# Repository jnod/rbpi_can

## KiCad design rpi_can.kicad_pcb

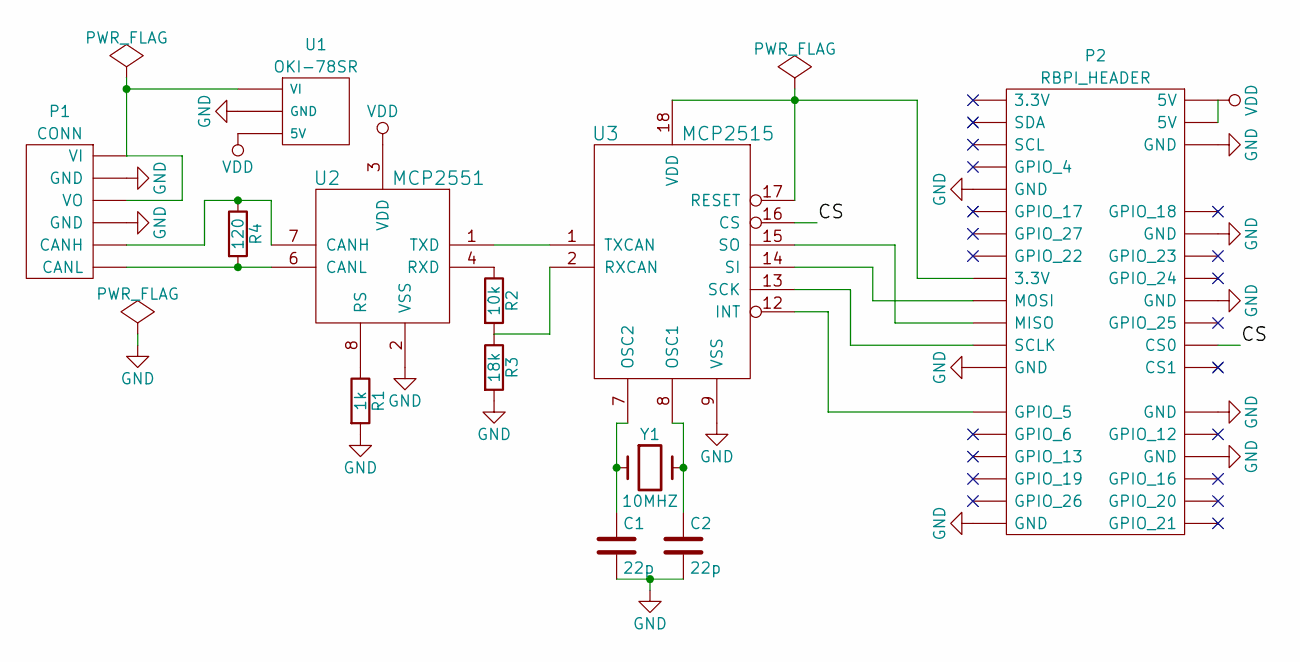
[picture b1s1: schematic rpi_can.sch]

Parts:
C1, C2: 22p; C_1206_HandSoldering
P1: CONN; Pin_Header_Straight_1x06
P2: RBPI_HEADER; Pin_Header_Straight_2x20
R1: 1k; R_1206_HandSoldering
R2: 10k; R_1206_HandSoldering
R3: 18k; R_1206_HandSoldering
R4: 120; R_1206_HandSoldering
U1: OKI-78SR
U2: MCP2551; DIP-8_W7.62mm
U3: MCP2515; DIP-18_W7.62mm
Y1: 10MHZ; Crystal_HC49-U_Vertical

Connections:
/CS: P2.24 (CS0), U3.16 (CS)
GND: C1.2, C2.2, P1.2 (GND), P1.4 (GND), P2.6 (GND), P2.9 (GND), P2.14 (GND), P2.20 (GND), P2.25 (GND), P2.30 (GND), P2.34 (GND), P2.39 (GND), R1.2, R3.2, U1.2 (GND), U2.2 (VSS), U3.9 (VSS)
unnamed: C1.1, U3.7 (OSC2), Y1.1
unnamed: C2.1, U3.8 (OSC1), Y1.2
unnamed: P1.1 (VI), P1.3 (VO), U1.1 (VI)
unnamed: P1.5 (CANH), R4.1, U2.7 (CANH)
unnamed: P1.6 (CANL), R4.2, U2.6 (CANL)
unnamed: P2.17 (3.3V), U3.17 (RESET), U3.18 (VDD)
unnamed: P2.19 (MOSI), U3.14 (SI)
unnamed: P2.21 (MISO), U3.15 (SO)
unnamed: P2.23 (SCLK), U3.13 (SCK)
unnamed: P2.29 (GPIO_5), U3.12 (INT)
unnamed: R1.1, U2.8 (RS)
unnamed: R2.1, U2.4 (RXD)
unnamed: R2.2, R3.1, U3.2 (RXCAN)
unnamed: U2.1 (TXD), U3.1 (TXCAN)
VDD: P2.2 (5V), P2.4 (5V), U1.3 (5V), U2.3 (VDD)

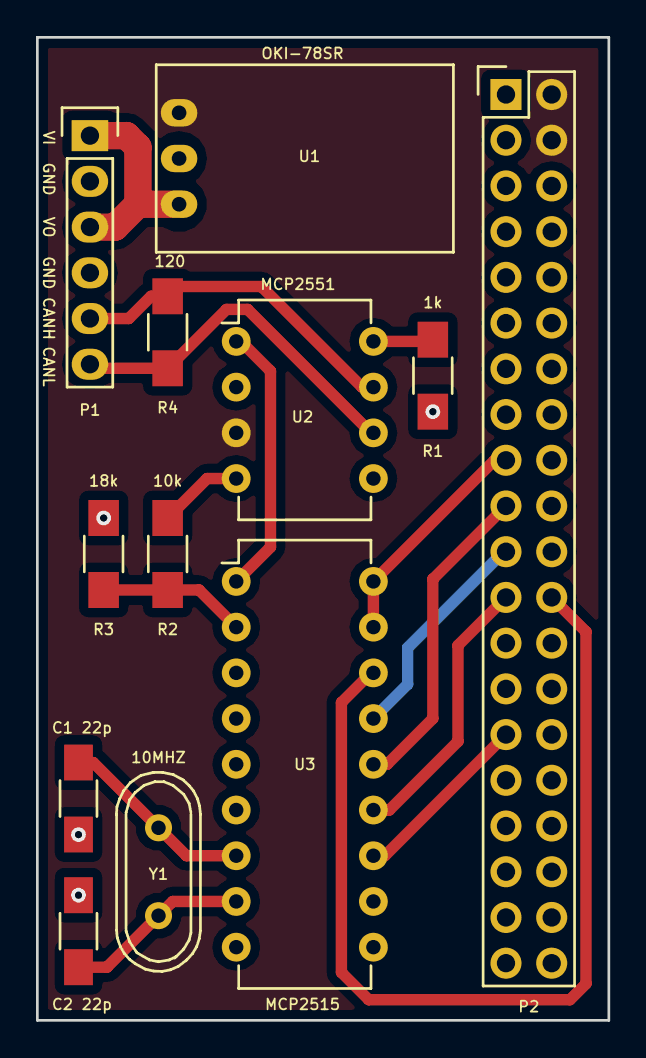
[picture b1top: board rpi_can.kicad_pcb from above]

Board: 2 copper layers, 31.8 x 54.6 mm, 12 parts (0 on the bottom side), 17 nets.

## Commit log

2016-01-10 Add schematic and PCB
2016-01-10 Clean up project
2016-02-22 Rename files
